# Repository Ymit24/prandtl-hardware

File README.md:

# ❄️🎛️ Too Hot To Prandtl Hardware

## About this repo
This repo contains all the hardware I designed for my undergraduate senior design project "Too Hot To Prandtl".

<!-- TABLE OF CONTENTS -->
<div>
  <h4>Table of Contents</h4>
  <ol>
    <li>
      <a href="#about-the-project">About The Project</a>
      <ul>
        <li><a href="#built-with">Built With</a></li>
      </ul>
    </li>
    <li><a href="#roadmap">Roadmap</a></li>
    <li><a href="#license">License</a></li>
    <li><a href="#contact">Contact</a></li>
  </ol>
</div>

## About the Project
My senior design project, "Too hot to prandtl", is a thermal management solution designed for heterogeniously packaged chips.
It is a fluid based cooler which leverages phase change to increase heat transfer.
Myself, along with four Mechnical Engineering students designed, simulated, fabricated, and tested this system.
As the teams sole Electrical Engineer, I wrote all the software and designed, ordered, assembled, and brought-up the custom embedded system's printed circuit board (PCB).
The software for this project is hosted in a seperate repository found [here](https://github.com/Ymit24/too-hot-to-prandtl-control-system/tree/main).

## Project Structure
This system is designed in KiCad. Any non-default symbols/footprints/models are located in the `lib/` directory and included in the custom symbols and footprints libraries.
Production files which were used for the prototype system are in the `production/` directory.

### Built With
- [KiCad](https://www.kicad.org), awesome free PCB designing tool!

## Roadmap
There are several design flaws in the first version of this system, all of which were able to be fixed in the lab so that the board was still operable.
Below are a few issues which I would address in a revision B, ordered from most severe to least.

- ESD protection diode is connected incorrectly. I misread the data sheet and connected the channels incorrectly.
- Serial wire debug header is both the wrong size/type and the footprint had a different pin labelling scheme than intended.
- Fan peripheral header needs power and ground connection.
- Use a single 8-bit/channel logic level shifter rather than eight individual 1-bit/channel shifters.
- Choose dimmer LEDs, the ones choosen are very bright.
- Fix typo in silkscreen for board name "Too Hot Too Prandtl" -> "Too Hot To Prandtl".

## License
This project uses the GNU General Purpose License (GPL). Basically, do whatever you want but you must open source any derivative work!

## Contact
My name is Christian Smith and you can contact me through my linked in [here](https://www.linkedin.com/in/christian-ryan-smith/).
As this was a senior design project which has now concluded, further work and support of this project will not continue.

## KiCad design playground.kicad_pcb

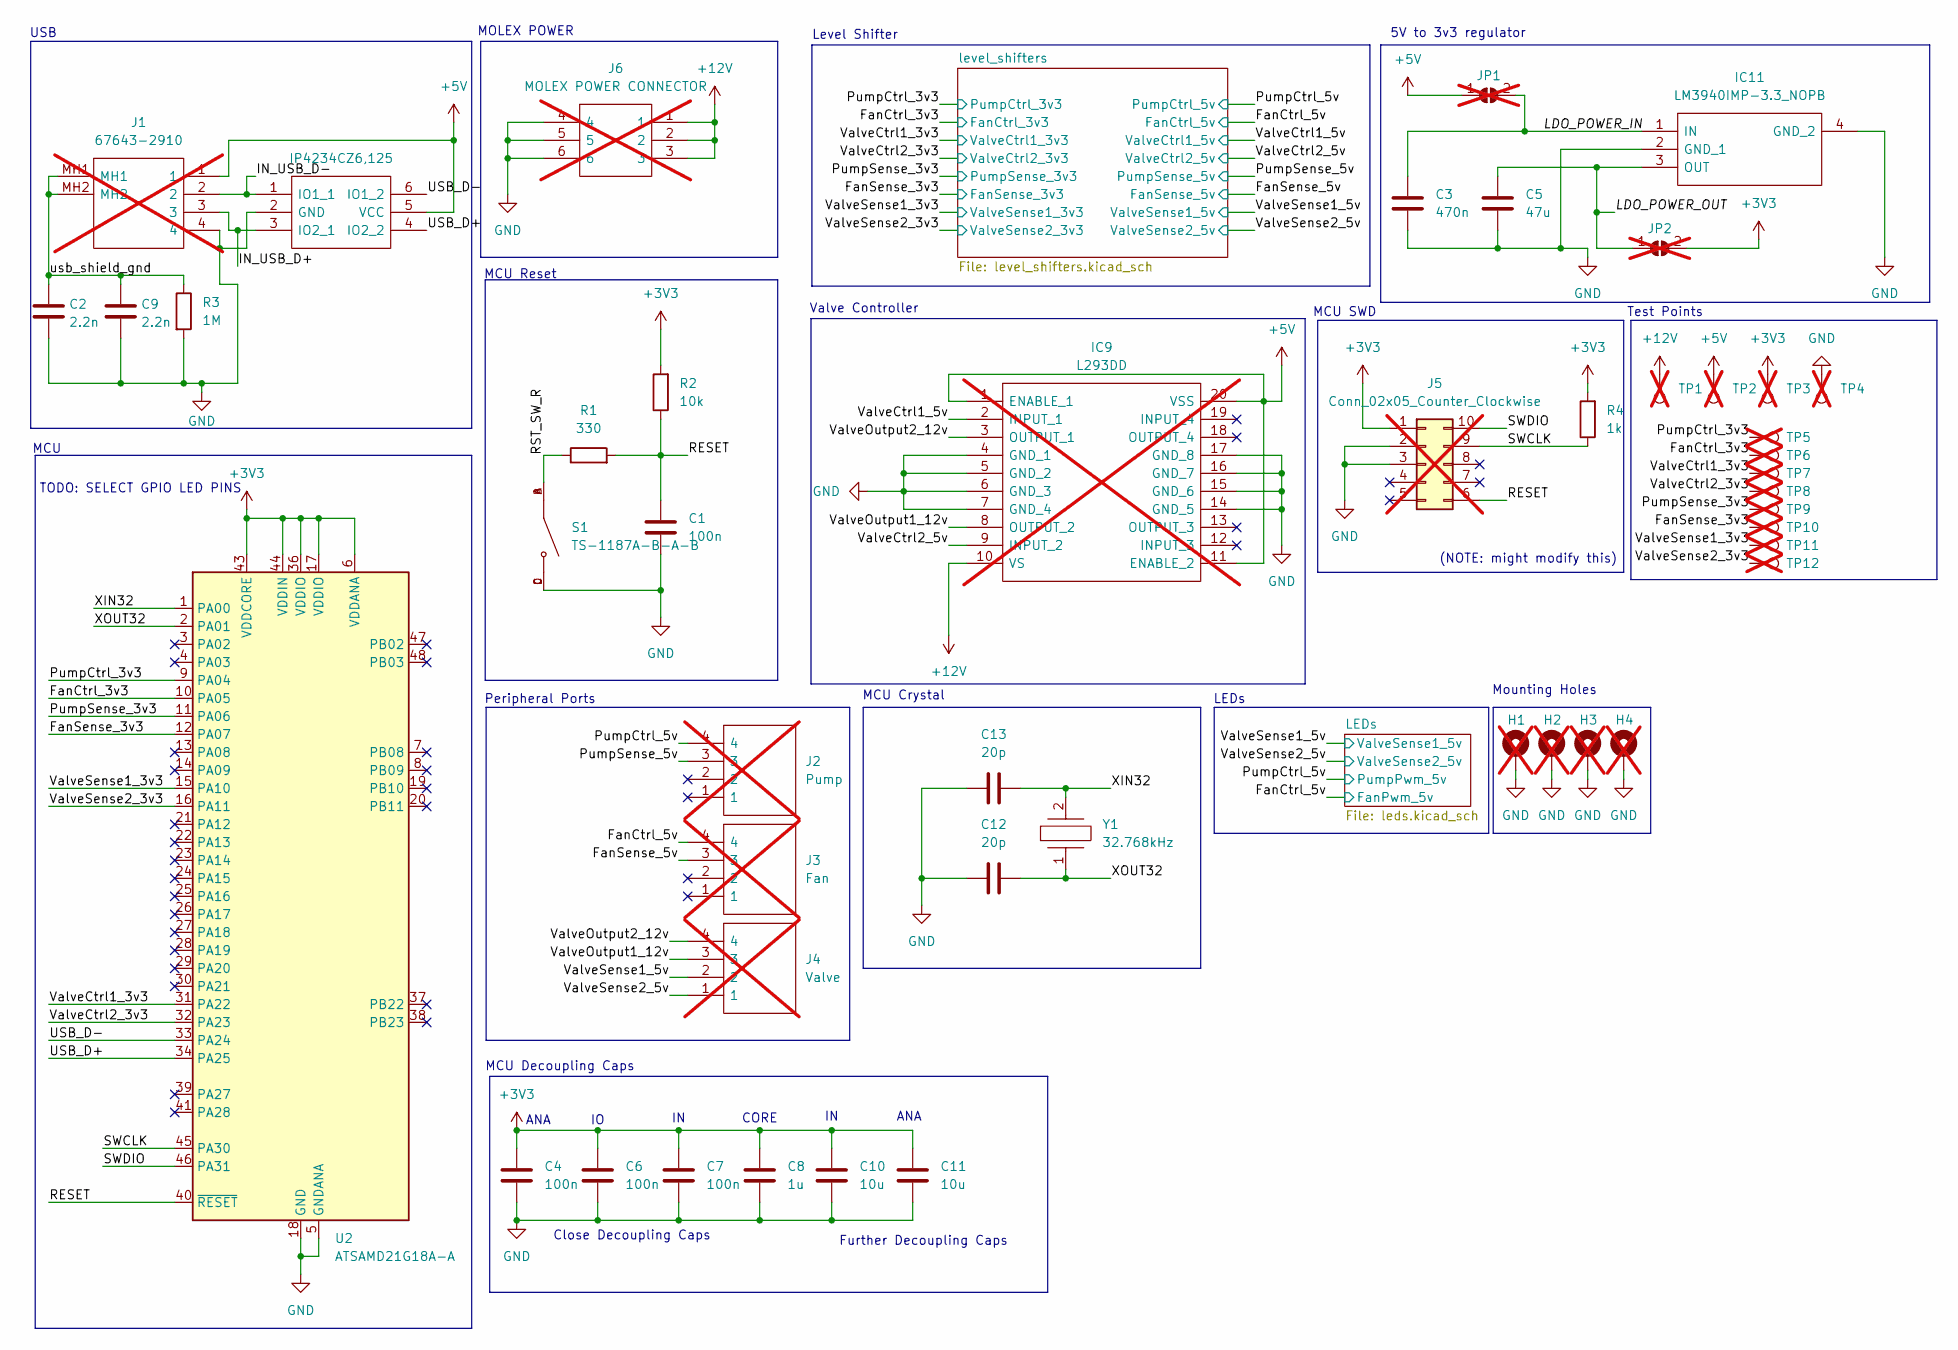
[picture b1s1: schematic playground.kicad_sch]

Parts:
C1, C4, C6, C7: 100n; C_0805_2012Metric; LCSC C49678
C2, C9: 2.2n; C_0805_2012Metric; LCSC C28260
C3: 470n; C_0805_2012Metric; LCSC C13967
C5: 47u; C_0805_2012Metric; LCSC C16780
C8: 1u; C_0805_2012Metric; LCSC C307362
C10, C11: 10u; C_0805_2012Metric; LCSC C15850
C12, C13: 20p; C_0805_2012Metric; LCSC C105173
D1: IP4234CZ6,125; SOP95P275X110-6N; Mouser Part Number 771-IP4234CZ6125
H1, H2, H3, H4: MountingHole_Pad; MountingHole_2.2mm_M2_Pad; not fitted
IC9: L293DD; SOIC127P1032X265-20N; Mouser Part Number 511-L293DD; not fitted
IC11: LM3940IMP-3.3_NOPB; SOT230P700X180-4N; Mouser Part Number 926-LM3940IMP3.3NOPB
J1: 67643-2910; 676432910; Mouser Part Number 538-67643-2910; not fitted
J2: Pump; 470531000; Mouser Part Number 538-47053-1000; not fitted
J3: Fan; 470531000; Mouser Part Number 538-47053-1000; not fitted
J4: Valve; 470531000; Mouser Part Number 538-47053-1000; not fitted
J5: Conn_02x05_Counter_Clockwise; PinHeader_2x05_P2.54mm_Vertical; not fitted
J6: MOLEX POWER CONNECTOR; 455580003; Mouser Part Number 538-45558-0003; not fitted
JP1, JP2: SolderJumper_2_Open; SolderJumper-2_P1.3mm_Open_Pad1.0x1.5mm; not fitted
R1: 330; R_0805_2012Metric; LCSC C17630
R2: 10k; R_0805_2012Metric; LCSC C17414
R3: 1M; R_0805_2012Metric; LCSC C17514
R4: 1k; R_0805_2012Metric; LCSC C17513
S1: TS-1187A-B-A-B; SW_TS-1187A-B-A-B; PARTREV A0; LCSC C318884
TP1, TP2, TP3, TP4, TP5, TP6, TP7, TP8, TP9, TP10, TP11, TP12: TestPoint; TestPoint_Pad_D1.0mm; not fitted
U2: ATSAMD21G18A-A; TQFP-48_7x7mm_P0.5mm; LCSC C78624
Y1: 32.768kHz; FC135327680KAA5; Mouser Part Number 732-532.7680KA-A5

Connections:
+3V3: C4.1, C6.1, C7.1, C8.1, C10.1, C11.1, J5.1, JP2.2 (B), R2.2, R4.2, TP3.1, U2.6 (VDDANA), U2.17 (VDDIO), U2.36 (VDDIO), U2.43 (VDDCORE), U2.44 (VDDIN); also elsewhere on the board
+5V: D1.5 (VCC), IC9.1 (ENABLE_1), IC9.11 (ENABLE_2), IC9.20 (VSS), J1.1, JP1.1 (A), TP2.1; also elsewhere on the board
+12V: IC9.10 (VS), J6.1, J6.2, J6.3, TP1.1; also elsewhere on the board
/FanCtrl_3v3: TP6.1, U2.10 (PA05); also elsewhere on the board
/FanCtrl_5v: J3.4; also elsewhere on the board
/FanSense_3v3: TP10.1, U2.12 (PA07); also elsewhere on the board
/FanSense_5v: J3.3; also elsewhere on the board
/IN_USB_D+: D1.3 (IO2_1), J1.3
/IN_USB_D-: D1.1 (IO1_1), J1.2
/LDO_POWER_IN: C3.1, IC11.1 (IN), JP1.2 (B)
/LDO_POWER_OUT: C5.1, IC11.3 (OUT), JP2.1 (A)
/PumpCtrl_3v3: TP5.1, U2.9 (PA04); also elsewhere on the board
/PumpCtrl_5v: J2.4; also elsewhere on the board
/PumpSense_3v3: TP9.1, U2.11 (PA06); also elsewhere on the board
/PumpSense_5v: J2.3; also elsewhere on the board
/RESET: C1.1, J5.6, R1.2, R2.1, U2.40 (~RESET)
/RST_SW_R: R1.1, S1.A, S1.B
/SWCLK: J5.9, R4.1, U2.45 (PA30)
/SWDIO: J5.10, U2.46 (PA31)
/USB_D+: D1.4 (IO2_2), U2.34 (PA25)
/USB_D-: D1.6 (IO1_2), U2.33 (PA24)
/ValveCtrl1_3v3: TP7.1, U2.31 (PA22); also elsewhere on the board
/ValveCtrl1_5v: IC9.2 (INPUT_1); also elsewhere on the board
/ValveCtrl2_3v3: TP8.1, U2.32 (PA23); also elsewhere on the board
/ValveCtrl2_5v: IC9.9 (INPUT_2); also elsewhere on the board
/ValveOutput1_12v: IC9.8 (OUTPUT_2), J4.3
/ValveOutput2_12v: IC9.3 (OUTPUT_1), J4.4
/ValveSense1_3v3: TP11.1, U2.15 (PA10); also elsewhere on the board
/ValveSense1_5v: J4.2; also elsewhere on the board
/ValveSense2_3v3: TP12.1, U2.16 (PA11); also elsewhere on the board
/ValveSense2_5v: J4.1; also elsewhere on the board
/XIN32: C13.2, U2.1 (PA00), Y1.2
/XOUT32: C12.2, U2.2 (PA01), Y1.1
/usb_shield_gnd: C2.1, C9.1, J1.MH1, J1.MH2, R3.1
GND: C1.2, C2.2, C3.2, C4.2, C5.2, C6.2, C7.2, C8.2, C9.2, C10.2, C11.2, C12.1, C13.1, D1.2 (GND), H1.1, H2.1, H3.1, H4.1, IC9.4 (GND_1), IC9.5 (GND_2), IC9.6 (GND_3), IC9.7 (GND_4), IC9.14 (GND_5), IC9.15 (GND_6), IC9.16 (GND_7), IC9.17 (GND_8), IC11.2 (GND_1), IC11.4 (GND_2), J1.4, J5.2, J5.3, J6.4, J6.5, J6.6, R3.2, S1.C, S1.D, TP4.1, U2.5 (GNDANA), U2.18 (GND), U2.35 (GND), U2.42 (GND); also elsewhere on the board

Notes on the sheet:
LEDs
Valve Controller
MCU Reset
Close Decoupling Caps
ANA
MOLEX POWER
TODO: SELECT GPIO LED PINS
MCU Decoupling Caps
Further Decoupling Caps
MCU Crystal
5V to 3v3 regulator
Mounting Holes
(NOTE: might modify this)
MCU SWD
USB
MCU
Level Shifter
Peripheral Ports
Test Points
CORE

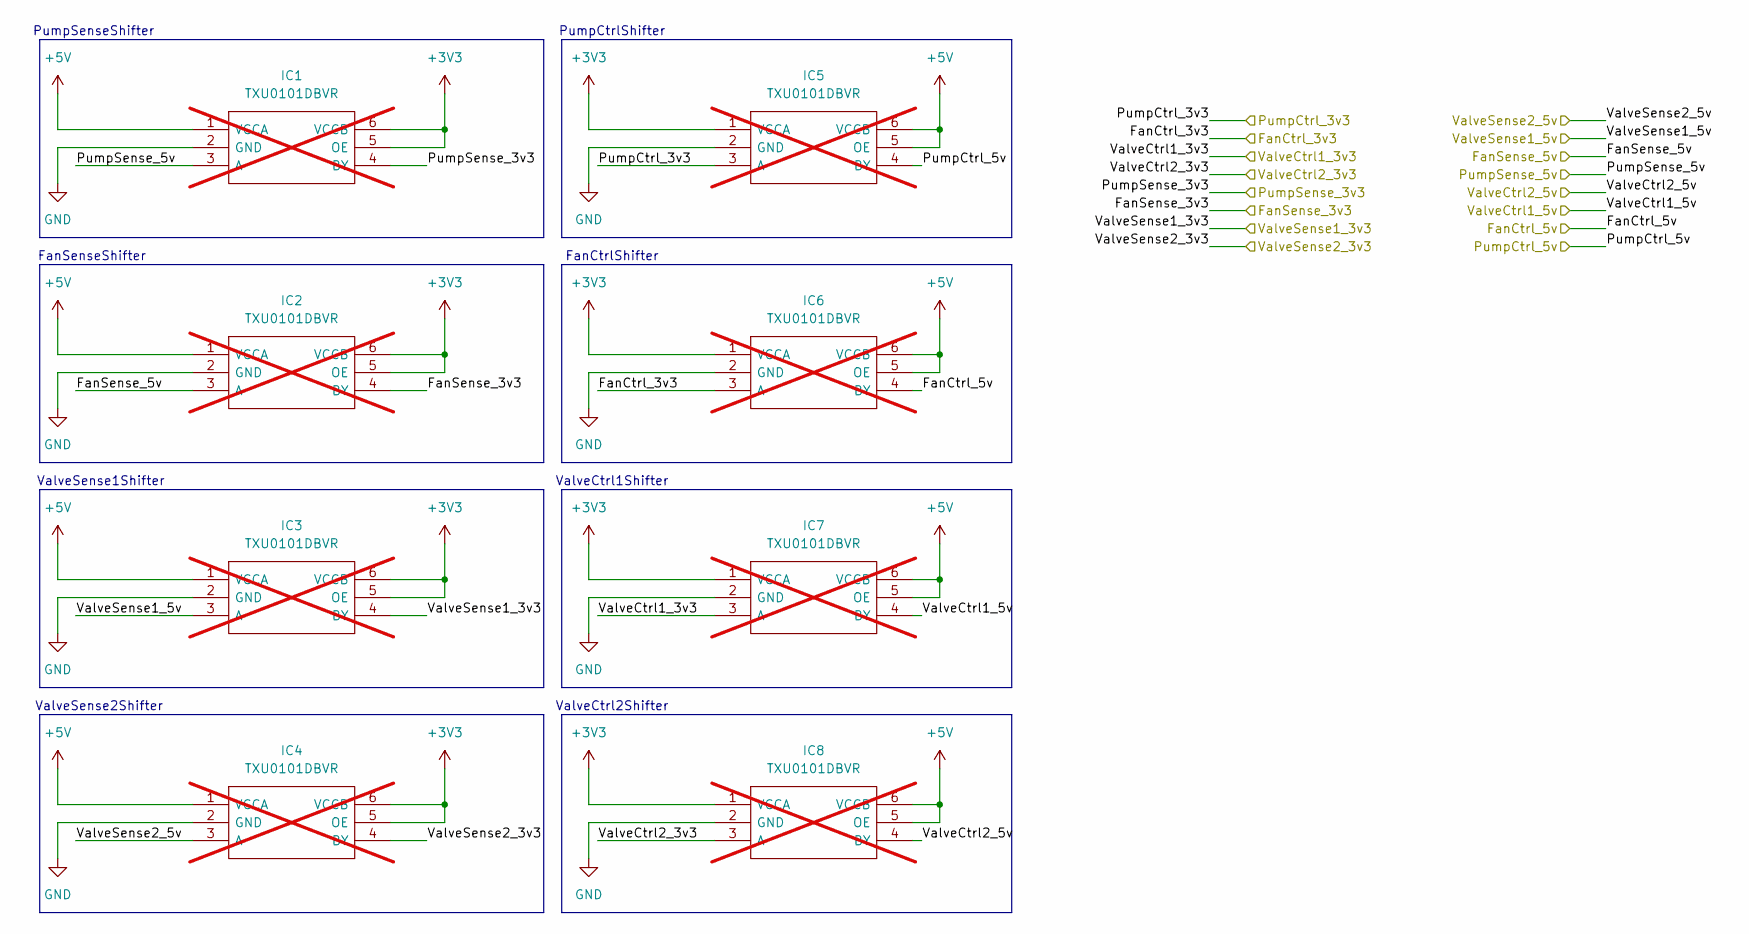
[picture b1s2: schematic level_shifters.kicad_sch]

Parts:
IC1, IC2, IC3, IC4, IC5, IC6, IC7, IC8: TXU0101DBVR; Mouser Part Number 595-TXU0101DBVR; not fitted

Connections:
+3V3: IC1.5 (OE), IC1.6 (VCCB), IC2.5 (OE), IC2.6 (VCCB), IC3.5 (OE), IC3.6 (VCCB), IC4.5 (OE), IC4.6 (VCCB), IC5.1 (VCCA), IC6.1 (VCCA), IC7.1 (VCCA), IC8.1 (VCCA); also elsewhere on the board
+5V: IC1.1 (VCCA), IC2.1 (VCCA), IC3.1 (VCCA), IC4.1 (VCCA), IC5.5 (OE), IC5.6 (VCCB), IC6.5 (OE), IC6.6 (VCCB), IC7.5 (OE), IC7.6 (VCCB), IC8.5 (OE), IC8.6 (VCCB); also elsewhere on the board
/FanCtrl_3v3: IC6.3 (A); also elsewhere on the board
/FanCtrl_5v: IC6.4 (BY); also elsewhere on the board
/FanSense_3v3: IC2.4 (BY); also elsewhere on the board
/FanSense_5v: IC2.3 (A); also elsewhere on the board
/PumpCtrl_3v3: IC5.3 (A); also elsewhere on the board
/PumpCtrl_5v: IC5.4 (BY); also elsewhere on the board
/PumpSense_3v3: IC1.4 (BY); also elsewhere on the board
/PumpSense_5v: IC1.3 (A); also elsewhere on the board
/ValveCtrl1_3v3: IC7.3 (A); also elsewhere on the board
/ValveCtrl1_5v: IC7.4 (BY); also elsewhere on the board
/ValveCtrl2_3v3: IC8.3 (A); also elsewhere on the board
/ValveCtrl2_5v: IC8.4 (BY); also elsewhere on the board
/ValveSense1_3v3: IC3.4 (BY); also elsewhere on the board
/ValveSense1_5v: IC3.3 (A); also elsewhere on the board
/ValveSense2_3v3: IC4.4 (BY); also elsewhere on the board
/ValveSense2_5v: IC4.3 (A); also elsewhere on the board
GND: IC1.2 (GND), IC2.2 (GND), IC3.2 (GND), IC4.2 (GND), IC5.2 (GND), IC6.2 (GND), IC7.2 (GND), IC8.2 (GND); also elsewhere on the board

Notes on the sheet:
ValveSense1Shifter
PumpCtrlShifter
ValveCtrl2Shifter
ValveSense2Shifter
FanCtrlShifter
PumpSenseShifter
ValveCtrl1Shifter
FanSenseShifter

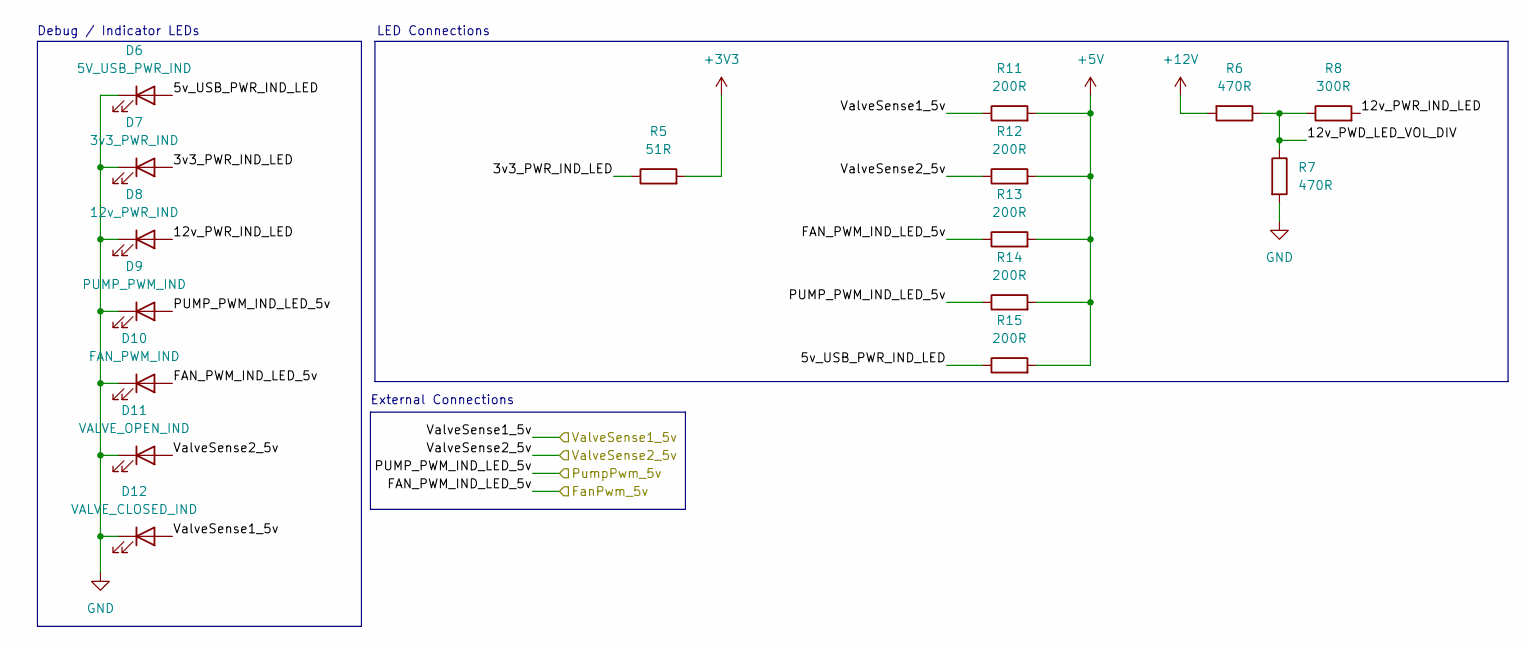
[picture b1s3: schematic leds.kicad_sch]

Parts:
D6: 5V_USB_PWR_IND; LED_0603_1608Metric; LCSC C2286
D7: 3v3_PWR_IND; LED_0603_1608Metric; LCSC C2286
D8: 12v_PWR_IND; LED_0603_1608Metric; LCSC C2286
D9: PUMP_PWM_IND; LED_0603_1608Metric; LCSC C2297
D10: FAN_PWM_IND; LED_0603_1608Metric; LCSC C2297
D11: VALVE_OPEN_IND; LED_0603_1608Metric; LCSC C2296
D12: VALVE_CLOSED_IND; LED_0603_1608Metric; LCSC C2296
R5: 51R; R_0805_2012Metric; MFR.Part # 0805W8F510JT5E; LCSC C17738
R6: 470R; R_0805_2012Metric; MFR.Part # 0805W8F4700T5E; LCSC C17738
R7: 470R; R_0805_2012Metric; LCSC C17738
R8: 300R; R_0805_2012Metric; MFR.Part # 1206W4F3000T5E; LCSC C17617
R11, R12, R13, R14, R15: 200R; R_0805_2012Metric; MFR.Part # 0805W8F200JT5E; LCSC C17540

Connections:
+3V3: R5.2; also elsewhere on the board
+5V: R11.2, R12.2, R13.2, R14.2, R15.2; also elsewhere on the board
+12V: R6.2; also elsewhere on the board
/FanCtrl_5v: D10.2 (A), R13.1; also elsewhere on the board
/LEDs/3v3_PWR_IND_LED: D7.2 (A), R5.1
/LEDs/5v_USB_PWR_IND_LED: D6.2 (A), R15.1
/LEDs/12v_PWD_LED_VOL_DIV: R6.1, R7.1, R8.1
/LEDs/12v_PWR_IND_LED: D8.2 (A), R8.2
/PumpCtrl_5v: D9.2 (A), R14.1; also elsewhere on the board
/ValveSense1_5v: D12.2 (A), R11.1; also elsewhere on the board
/ValveSense2_5v: D11.2 (A), R12.1; also elsewhere on the board
GND: D6.1 (K), D7.1 (K), D8.1 (K), D9.1 (K), D10.1 (K), D11.1 (K), D12.1 (K), R7.2; also elsewhere on the board

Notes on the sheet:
Debug / Indicator LEDs
External Connections
LED Connections

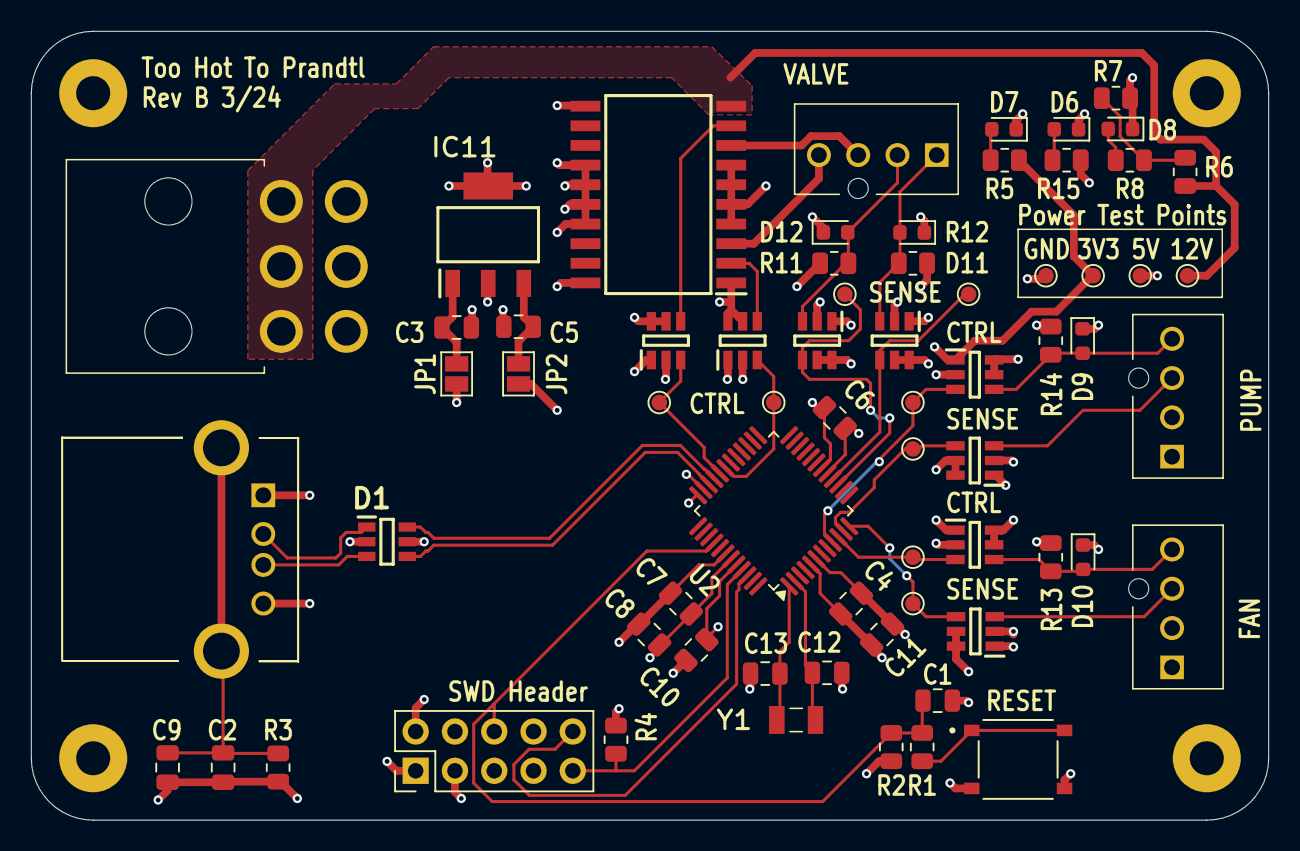
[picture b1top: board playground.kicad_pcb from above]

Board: 4 copper layers, 80.0 x 51.0 mm, 71 parts (0 on the bottom side), 39 nets.

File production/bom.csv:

Designator,Footprint,Quantity,Value,LCSC Part #
"C1, C4, C6, C7",0805,4,100n,C49678
"C10, C11",0805,2,10u,C15850
"C12, C13",0805,2,20p,C105173
"C2, C9",0805,2,2.2n,C28260
C3,0805,1,470n,C13967
C5,0805,1,47u,C16780
C8,0805,1,1u,C307362
D1,SOP95P275X110-6N,1,"IP4234CZ6,125",C455086
D10,0603,1,FAN_PWM_IND,C2297
D11,0603,1,VALVE_OPEN_IND,C2296
D12,0603,1,VALVE_CLOSED_IND,C2296
D6,0603,1,5V_USB_PWR_IND,C2286
D7,0603,1,3v3_PWR_IND,C2286
D8,0603,1,12v_PWR_IND,C2286
D9,0603,1,PUMP_PWM_IND,C2297
IC11,SOT230P700X180-4N,1,LM3940IMP-3.3_NOPB,C140319
R1,0805,1,330,C17630
"R11, R12, R13, R14, R15",0805,5,200R,C17540
R2,0805,1,10k,C17414
R3,0805,1,1M,C17514
R4,0805,1,1k,C17513
R5,0805,1,51R,C17738
"R6, R7",0805,2,470R,C17738
R8,0805,1,300R,C17617
S1,SW_TS-1187A-B-A-B,1,TS-1187A-B-A-B,C318884
U2,TQFP-48_7x7mm_P0.5mm,1,ATSAMD21G18A-A,C78624
Y1,FC135327680KAA5,1,32.768kHz,C32346

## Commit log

2024-02-25 init
2024-02-25 did basic routing. Still missing some parts.
2024-03-16 storing local changes.
2024-03-20 saving progress
2024-03-20 Added LEDs and testpoints
2024-03-21 removed jumpers
2024-03-21 Changed board size to 80x80mm
2024-03-22 Updated layout and schem
2024-03-23 Layout of indicator LEDs. Shrank design space
2024-03-23 Reduced board size
2024-03-23 Initial Routing
2024-03-23 Completed intial 2-layer routing.
2024-03-23 Initial Layout
2024-03-23 Fixed board outline
2024-03-24 Layout and Route of 4 layer version complete.
2024-03-24 2Layer complete
2024-03-24 Modified layout. Added more silkscreen.
2024-03-24 Prepare to gather part #s and generate prod files
2024-03-24 Fixed all DRC issues
2024-03-24 Small part substitutions. Working on BOM
2024-03-25 Add JLCPCB part numbers.
2024-03-26 Added all part numbers
2024-03-26 Prepped for production.
2024-03-26 Version exported for production.
2024-03-26 Took pictures of PCB
2024-03-26 Cleaned up project files
2024-03-26 Fixed spelling of 'Too hot _to_ prandtl'. Now rev B
2024-03-26 (part of last commit)
2024-05-13 Create README.md
    Add README to repository.
2024-05-13 Create LICENSE.txt
    Added the GPL2 License
2024-05-13 add gitignore
2024-05-13 renamed project
2024-05-13 removed old power regulator files
2024-05-13 Remove .DS_Store
